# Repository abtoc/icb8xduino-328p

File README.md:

ICB8xduino-328p(kicadプロジェクト一式)
====

ボードサイズをサンハヤト社製のICB-86,ICB-87のサイズに合わせたArduino互換基板です。
Arduino上でハードウェアのプロトタイプ作成者向けのボードになります。

目的とするシールドが無い場合は、ハードウェアの実装が必要になります。
が、下記のような問題に直面すると思います。

- 専用のユニバーサル基板を使用しなければならない
- 専用のユニバーサル基板の種類が限られる
- 100milピッチではないコネクタのため、アートワークが困難

本基板は、上記を考慮し、Arduinoプラットフォーム上で、
ハードウェア・プロトタイプ開発の手助けができれば幸いです。

## 特徴
- サイズはICB-86,ICB-87相当としています
- 基板の角のそれぞれにATmega328pのピンを全てアサインしています  
  また、ICB-86,ICB-87のコネクタパターンに合うよう配置しています

## 仕様
- ATmega328pで動作します
- クロックは16MHzクリスタル・レゾネータ及びインターナルクロック(8MHz)で動作可能です
- デジタルとアナログの電源はジャンパで分離しています
- 電源はUSBシリアル変換アダプター、ACアダプタ(コネクタ上のVINも含む)です  

## 使用方法
### 内容について
- kicadのプロジェクトファイル一式が入れられております
- ガーバーデータは garberディレクトリ に格納しております

|No. |ファイル名                   |種類                      |
|---:|:----------------------------|:-------------------------|
|1   |ICB8xduino-328p-F.Cu.gtl     |トップレイヤ              |
|2   |ICB8xduino-328p-B.Cu.gbl     |ボトムレイヤ              |
|3   |ICB8xduino-328p-F.Mask.gts   |表面ソルダレジスト        |
|4   |ICB8xduino-328p-B.Mask.gbs   |裏面ソルダレジスト        |
|5   |ICB8xduino-328p-F.SilkS.gto  |表面シルク                |
|6   |ICB8xduino-328p-B.SilkS.gbo  |裏面シルク                |
|7   |ICB8xduino-328p-Edge.Cuts.gm1|基板外形                  |
|8   |ICB8xduino-328p.drl          |スルーホール有ドリルデータ|
|9   |ICB8xduino-328p-NPTH.drl     |スルーホール無ドリルデータ|

### [回路図](ICB8xduino-328p.pdf)

### パターン
- 前面  

- 背面  

### 部品表
|No. |Reference	 |部品名                                      |備考|
|---:|:----------|:-------------------------------------------|:---| 
|1   |C1	       |積層セラミックコンデンサ 0.1μF             |    |
|2   |C2       	 |電解コンデンサ 47μF                        |    |
|3   |C3         |電解コンデンサ 47μF                        |    |
|4   |C4         |積層セラミックコンデンサ 0.1μF             |    |
|5   |C5  	     |積層セラミックコンデンサ 22pF               |インターナルクロック、レゾネータ使用時は不要|
|6   |C6	       |積層セラミックコンデンサ 22pF               |インターナルクロック、レゾネータ使用時は不要|
|7   |C7	       |積層セラミックコンデンサ 0.1μF             |    |
|8   |C8         |積層セラミックコンデンサ 0.1μF             |    |
|9   |C9 	       |積層セラミックコンデンサ 0.1μF             |    |
|10  |CONN1      |1x8 2.54mmピッチ ピンフレーム               |    |
|11  |CONN2	     |1x8 2.54mmピッチ ピンフレーム               |    |
|12  |CONN3	     |1x8 2.54mmピッチ ピンフレーム               |    |
|13  |CONN4	     |1x8 2.54mmピッチ ピンフレーム               |    |
|14  |CONN5	     |2x3 2.54mmピッチ ピンヘッダ                 |    |
|15  |D1	       |3mm LED(赤)                                 |    |
|16  |D2	       |3mm LED(緑)                                 |    |
|17  |J1	       |2.1mm標準DCジャック                         |    |
|18  |J2 	       |1x6 2.54mmピッチ ピンヘッダ(L型)            |    |
|19  |(J4)       |秋月電子 AE-FT234X 用端子                   |AT-FT234Xを使いたい場合に実装してください|
|20  |JP1	       |2x3 2.54mmピッチ ピンヘッダ                 |    |
|21  |(JP1)      |2.54ピッチ・ジャンパーピン                  |    |
|22  |R1      	 |炭素皮膜抵抗器 10KΩ 1/4W (茶黒橙)          |    |
|23  |R2  	     |炭素皮膜抵抗器 330Ω 1/4W (橙橙茶)          |    |
|24  |R3	       |炭素皮膜抵抗器 10KΩ 1/4W (茶黒橙)          |    |
|25  |R4	       |炭素皮膜抵抗器 330Ω 1/4W (橙橙茶)          |    |
|26  |R5	       |炭素皮膜抵抗器 330Ω 1/4W (橙橙茶)          |    |
|27  |SW1	       |タクトスイッチ                              |    |
|28  |U1	       |三端子レギュレータ 5V0.5A                   |    |
|29  |U2	       |ATMEGA328P-PU                               |    |
|30  |(U2)       |ICソケット(28ピン,300mil)                   |    |
|31  |Y1         |水晶振動子(16MHz)又はセラミック発振子(16MHz)|インターナルクロックの場合は不要|

### 実装
- GS1,GS2はハンダで接続してください。
- 内蔵クロックを使用する場合は、C5,C6及びクリスタルの実装は必要ありません。
- レゾネータを使用する場合は、C5,C6の実装は必要ありません。
- 電源をDCアダプタ(VIN端子含む)・USBシリアル変換アダプターのどちらかを、  
  ジャンパーで選択してください(回路図中JP1)
- Arduinoとして使用する場合は、AVRISP mk2でブートローダを書き込んでください  
  ブートローダ書き込み済のマイコンを使用する場合は不要です。また、
  ISCP端子も不要です
- ACアダプタの電源は三端子レギュレータの仕様に従ってください  
  本回路では12〜35Vを想定してます、

### ブートローダー書込
Arduinoとして使用する場合は、ブートローダーを書き込んでください  
※AVRISP mk2で書き込む場合

#### クリスタル、レゾネーターで使用する場合
```
avrdude \
-P usb            \
-b 19200          \
-c avrisp2        \
-p m328p          \
-v -e             \
-U efuse:w:0xFD:m \
-U hfuse:w:0xD6:m \
-U lfuse:w:0xFF:m

avrdude           \
-P usb            \
-b 19200          \
-c avrisp2        \
-p m328p          \
-v -e             \
-U lock:w:0xCF:m  \
-U flash:w:optiboot/optiboot_atmega328.hex

```

####  インターナル・クロックで使用する場合
```
avrdude \
-P usb            \
-b 19200          \
-c avrisp2        \
-p m328p          \
-v -e             \
-U efuse:w:0xFD:m \
-U hfuse:w:0xDA:m \
-U lfuse:w:0xE2:m

avrdude           \
-P usb            \
-b 19200          \
-c avrisp2        \
-p m328p          \
-v -e             \
-U lock:w:0xCF:m  \
-U flash:w:ATmegaBOOT_168_atmega328_pro_8MHz.hex
```
### スケッチ書き込み(Arduino IDE)
- スケッチの書き込みはUSBシリアル変換アダプターを使用してください  
  ピンアサインはArduino Proと同等にしてあります
- ボードの選択は下記の通りです
  - クリスタル、レゾネータの場合
    - ボード：Arduino/Genuino UNO
  - インターナルクロックの場合
    - ボード；Arduino Pro or Pro mini
    - プロセッサ：ATmega328P(3.3V, 8MHz)
- シリアルポートはUSBシリアル変換アダプターのポートを使用してください

## コネクタ
### CONN1
|No  |Aduino |ATmega328p |Pin |備考 |
|---:|-------|-----------|---:|-----|
|1   |GNDD   |GND        |8   |     |
|2   |RESET  |#RESET     |1   |     |
|3   |0      |PD0/RXD    |2   |     |
|4   |1      |PD1/TXD    |3   |     |
|5   |2      |PD2        |4   |     |
|6   |3      |PD3        |5   |     |
|7   |4      |PD4        |6   |     |
|8   |VDD    |VCC        |7   |     |

### CONN2
|No  |Aduino |ATmega328p |Pin |備考                     |
|---:|-------|-----------|---:|-------------------------|
|1   |GNDD   |GND        |8   |                         |
|2   |XTAL1  |PB6        |9   |内蔵クロックのみ使用可能 |
|3   |XTAL2  |PB7        |10  |内蔵クロックのみ使用可能 |
|4   |5      |PD5        |11  |                         |
|5   |6      |PD6        |12  |                         |
|6   |7      |PD7        |13  |                         |
|7   |8      |PB0        |14  |                         |
|8   |VIN    |VIN        |-   |３端子レギュレータ入力   |

### CONN3
|No  |Aduino |ATmega328p |Pin |備考         |
|---:|-------|-----------|---:|-------------|
|1   |9      |PB1        |15  |             |
|2   |10     |PB2/SS     |16  |             |
|3   |11     |PB3/MOSI   |17  |             |
|4   |12     |PB4/MISO   |18  |             |
|5   |13     |PB5/SCK    |19  |             |
|6   |VCC    |AVCC       |20  |アナログ電源 |
|7   |AREF   |AREF       |21  |             |
|8   |GNDA   |GND        |22  |アナログ電源 |

### CONN4
|No  |Aduino |ATmega328p |Pin |備考 |
|---:|-------|-----------|---:|-----|
|1   |A0     |PC0        |23  |     |
|2   |A1     |PC1        |24  |     |
|3   |A2     |PC2        |25  |     |
|4   |A3     |PC3        |26  |     |
|5   |A4     |PC4/SDA    |27  |     |
|6   |A5     |PC5/SCL    |28  |     |
|7   |GNDD   |GND        |8   |     |
|8   |VDD    |VCC        |7   |     |

## ライセンス

基板のアートワークについては[クリエイティブ・コモンズ 表示 - 非営利 4.0 国際 ライセンス](http://creativecommons.org/licenses/by-nc/4.0/)の下に提供されています。

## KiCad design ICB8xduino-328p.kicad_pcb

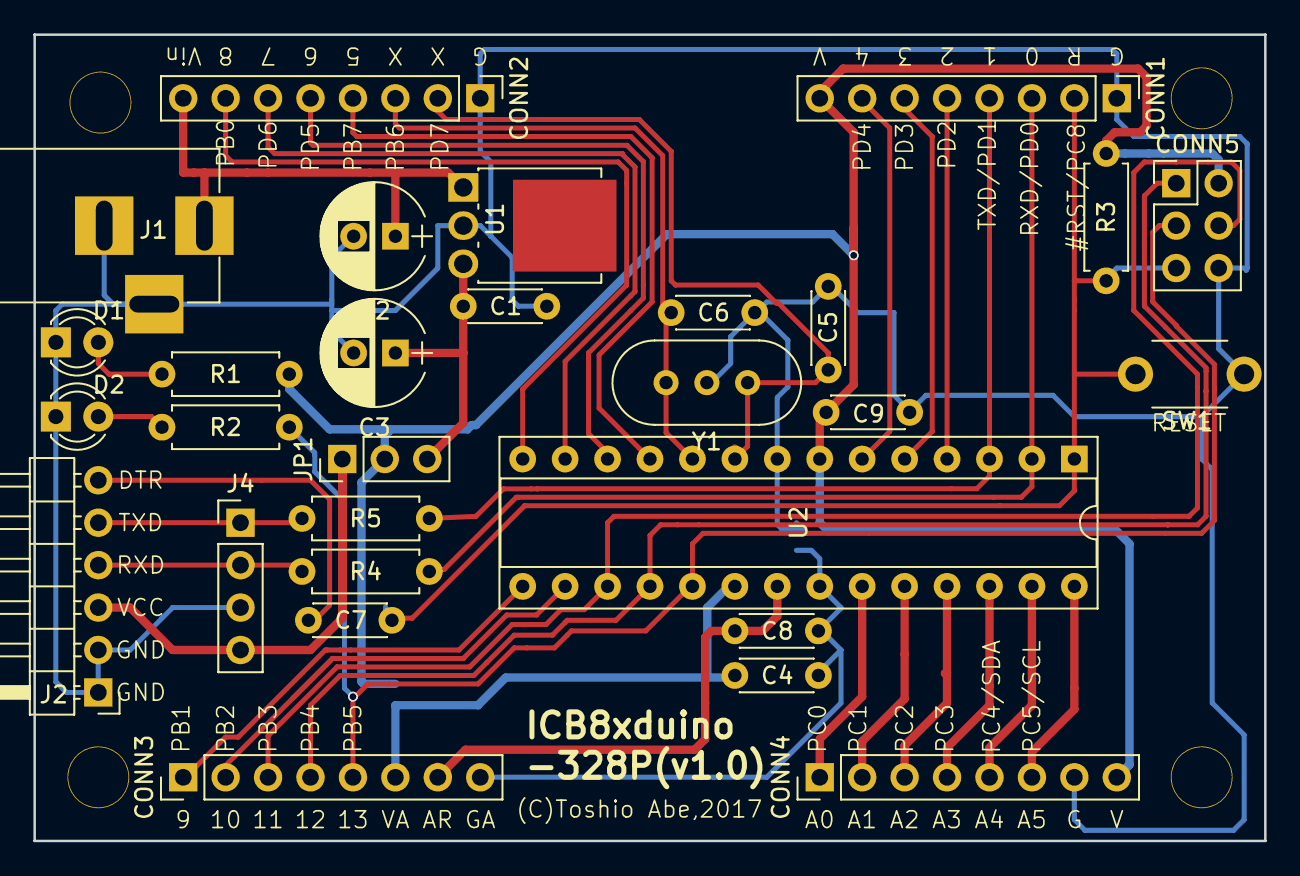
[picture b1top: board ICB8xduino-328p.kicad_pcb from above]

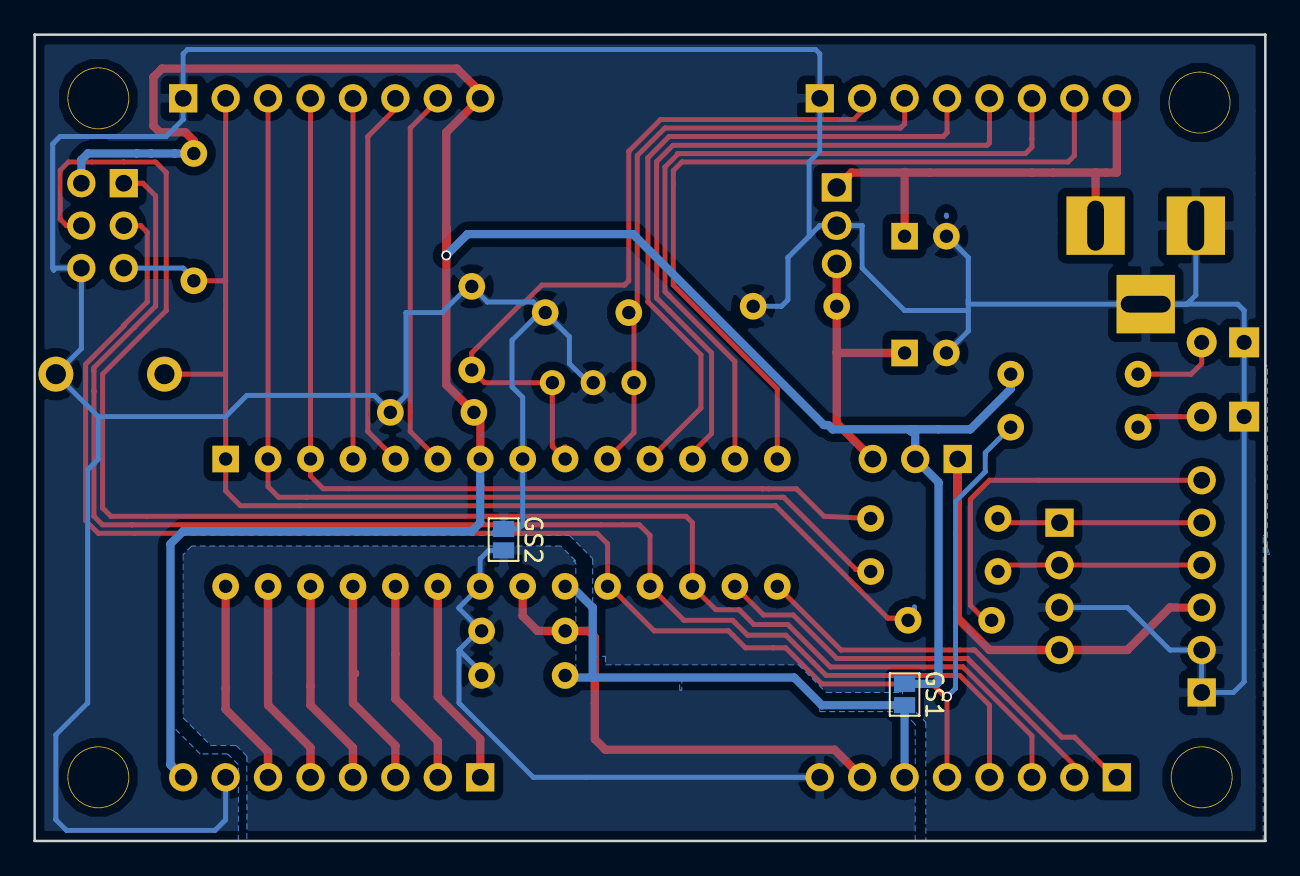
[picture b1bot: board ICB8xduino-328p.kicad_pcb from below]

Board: 2 copper layers, 73.7 x 48.3 mm, 31 parts (2 on the bottom side), 36 nets.

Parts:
C1, C4, C7, C8, C9: 0.1u; C_Disc_D4.3mm_W1.9mm_P5.00mm
C2, C3: 47u; CP_Radial_D6.3mm_P2.50mm
C5, C6: 22p; C_Disc_D4.3mm_W1.9mm_P5.00mm
CONN1: 1-7; Pin_Header_Straight_1x08_Pitch2.54mm
CONN2: 8-14; Pin_Header_Straight_1x08_Pitch2.54mm
CONN3: 15-22; Pin_Header_Straight_1x08_Pitch2.54mm
CONN4: 23-28; Pin_Header_Straight_1x08_Pitch2.54mm
CONN5: ICSP; Pin_Header_Straight_2x03_Pitch2.54mm
D1: RED; LED_D3.0mm
D2: GREEN; LED_D3.0mm
GS1: POWER; GS2
GS2: GND; GS2
J1: BARREL_JACK
J2: Serial; Pin_Header_Angled_1x06_Pitch2.54mm
J4: AE-FT234X; Pin_Header_Straight_1x04_Pitch2.54mm
JP1: PWR; Pin_Header_Straight_1x03_Pitch2.54mm
R1, R3: 10k; R_Axial_DIN0207_L6.3mm_D2.5mm_P7.62mm_Horizontal
R2, R4, R5: 330; R_Axial_DIN0207_L6.3mm_D2.5mm_P7.62mm_Horizontal
SW1: RESET; SW_PUSH_Single_6mm
U1: TA78M05F; SIPAK-1EP_Horizontal
U2: ATMEGA328-PU; DIP-28_W7.62mm_Socket
Y1: 16MHz; Resonator__HC49-U_Vertical

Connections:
/0: CONN1.3, R4.1, U2.2
/1: CONN1.4, R5.1, U2.3
/2: CONN1.5, U2.4
/3: CONN1.6, U2.5
/4: CONN1.7, U2.6
/5: CONN2.4, U2.11
/6: CONN2.5, U2.12
/7: CONN2.6, U2.13
/8: CONN2.7, U2.14
/9: CONN3.1, U2.15
/10: CONN3.2, U2.16
/11: CONN3.3, CONN5.4, U2.17
/12: CONN3.4, CONN5.1, U2.18
/13: CONN3.5, CONN5.3, R2.1, U2.19
/A0: CONN4.1, U2.23
/A1: CONN4.2, U2.24
/A2: CONN4.3, U2.25
/A3: CONN4.4, U2.26
/A4: CONN4.5, U2.27
/A5: CONN4.6, U2.28
/AREF: C8.1, CONN3.7, U2.21
/DC: C1.1, C3.1, JP1.3, U1.3
/DTR: C7.1, J2.6
/RESET: C7.2, CONN1.2, CONN5.5, R3.2, SW1.2, U2.1
/RXD: J2.4, J4.2, R4.2
/TXD: J2.5, J4.1, R5.2
/V: J2.3, J4.4, JP1.1
/VIN: C2.1, CONN2.8, J1.1, U1.1
/XTAL1: C5.1, CONN2.2, U2.9, Y1.1
/XTAL2: C6.1, CONN2.3, U2.10, Y1.3
GNDA: C4.2, C8.2, CONN3.8, GS2.2, U2.22
GNDD: C1.2, C2.2, C3.2, C5.2, C6.2, C9.2, CONN1.1, CONN2.1, CONN4.7, CONN5.6, D1.1, D2.1, GS2.1, J1.2, J1.3, J2.1, J2.2, J4.3, SW1.1, U1.2, U2.8, Y1.2
unnamed: D1.2, R1.2
unnamed: D2.2, R2.2
VCC: C4.1, CONN3.6, GS1.2, U2.20
VDD: C9.1, CONN1.8, CONN4.8, CONN5.2, GS1.1, JP1.2, R1.1, R3.1, U2.7

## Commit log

2018-01-19 Version 1.0版完成
2018-01-19 README.mdの一部を変更
2018-01-31 個別ライブラリをプロジェクトに入れた
2018-02-01 全体完成
2018-02-01 画像、ガーバーデータ追加
2018-02-06 README.md見直し及びガーバーデータ作成
2018-02-06 README.md見直し
2018-03-02 画像サイズ変更

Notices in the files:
README.md:
CC BY-NC 4.0
